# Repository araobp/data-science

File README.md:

# Edge AI and Digital Signal Processing

Hand gesture "Paper" captured with [AMG8833 infrared array sensor (8x8 resolution)](https://industrial.panasonic.com/products/pt/grid-eye/models/AMG8833), and its DCT Type-II coefficients.

Paco de Lucia's Picado from ["Cepa Andaluza" (Bulerias)](https://youtu.be/NIKWBdthzg4?si=O71p1-v_ynUPurbq) captured with my "Acoustic Feature Camera" device.

In this project, I pick up some of my achievements on edge AI from my past projects, and update them with the latest IDEs such as STM32CubeIDE or Android Studio.

I will also try to create Generative Art with edge AI in this project.

My past projects on edge AI:
- [acoustic-features](https://github.com/araobp/acoustic-features)
- [android-aed](https://github.com/araobp/android-aed)
- [stm32-mcu](https://github.com/araobp/stm32-mcu)

## Project 1: Rock Paper Scissors Machine

- "Rock Paper Scissors" game machine with NUCLEO-L476RG board.
- Digital Twin of the machine made with Blender.

=> **[Rock Paper Scissors](./RockPaperScissors)**

## Project 2: Acoustic Scene Classification (Work in progress)

Note: I have stopped developing this on STM32L4, because X-CUBE-AI has some problems. I will start developing Acoustic Scene Classification on Android instead.

=> **[Acoustic Scene Classification with Android (work in progress)](./AcousticSceneClassification)**

=> [Audio Signal Processing with STM32L4 (terminated)](./AudioSignalProcessingWithSTM32L4.md)

---
## Misc

### [Arduino-version of the thermography](misc/Arduino)

Make Jupyter Notebook collect data from this Arduino version of the thermograpy device with Panasonic AMG8833.

This is me.

### Learning by Doing

### DSP-related

- [Digital Audio Processing](misc/DigitalAudioProcessing)
- [Speech Processing for AI](misc/SpeechProcessing)

### Others

- [CIFAR 10](misc/CIFAR10): The best accuracy I have ever achieved is 75%...
- [MINIST](misc/MNIST)
- [IMDb](misc/IMDb)
- [Titanic](misc/Titanic)
- [Audio](misc/Audio)

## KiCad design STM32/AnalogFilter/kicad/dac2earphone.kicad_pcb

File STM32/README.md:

# Rock Paper Scissors with CubeIDE and STM32Cube.AI

Board: NUCLEO-L476RG board (STM32L476RGT6 Microcontroller)

### Arudino shield for Panasonic AMG8833

I designed my original Arduino shield for AMG8833 in 2019. Refer to [this page](https://github.com/araobp/stm32-mcu/tree/master/NUCLEO-F401RE/Thermography). I use this board with Nucleo L476RG.

=> [Schematic](https://github.com/araobp/stm32-mcu/blob/master/NUCLEO-F401RE/Thermography/kicad/arduino_board.pdf)

### Thermography (without AI)

This project is just a thermography app with Panasonic AMG8833 (no AI):
- [Thermography](Thermography)

Its GUI is in this folder: [GUI(Python3)](Thermography/GUI)

```
[NUCLEO L476RG] --- UART (VCP via ST-Link) --- COM port [Thermography GUI]
```

### Rock Paper Scissors (with AI)

This project is AI Rock Paper Scissors with Panasonic AMG8333:
- [RockPaperScissors](RockPaperScissors)

Its recognition performance is good.

This experiment proves that twenty of DCT Type-II coefficients with a small DNN is sufficient for recognizing rock/paper/scissors. 

### CubeMX-related problems I faced in this development

***printf issues***

I faced malloc-related build errors after I added "printf" (_write() function) to "main.c". The following setting solved the problem.

The marked part must be elased.

***Build errors***

Building with source code generated by X-Cube-AI results in a lot of errors. Building twice resolves this problem. Why?

***Lack of documentation***

I need example source codes of STM32Cube.AI. This page might help:
https://wiki.stmicroelectronics.cn/stm32mcu/wiki/AI:How_to_perform_motion_sensing_on_STM32L4_IoTnode#Add_AI_bootstrapping_functions

## Other Basic apps (not relevant to Rock Paper Scissors)

- [HelloWorld](HelloWorld)
- [Clock](Clock)

### I2C pin assignment for Arduino shield

Arduino shield uses PB8 and PB9 for I2C SCL and SDA.

## References

### CMSIS-DSP library

Refer to the following site: Google search "Configuring DSP libraries on STM32CubeIDE"

[API reference](https://arm-software.github.io/CMSIS_5/General/html/index.html)

## References

- https://stackoverflow.com/questions/59395181/cmsis-dsp-in-stm32cubeide

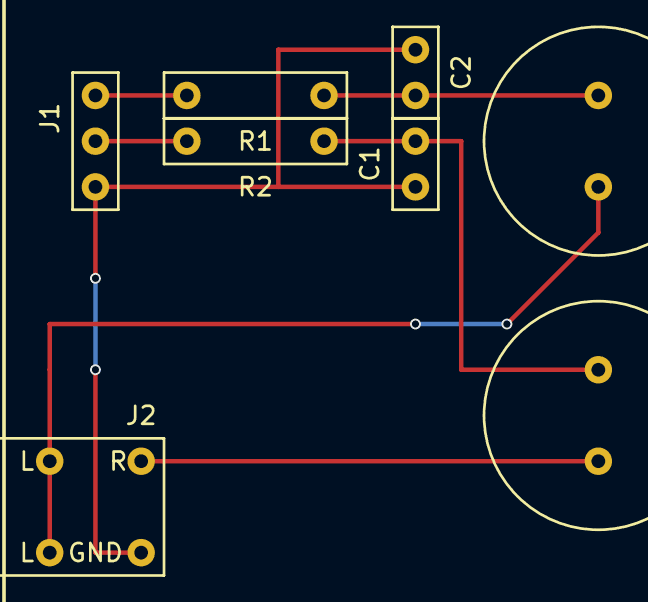
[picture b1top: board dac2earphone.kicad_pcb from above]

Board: 2 copper layers, 8 parts (0 on the bottom side), 7 nets.

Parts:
C1, C2: 0.1u; Capacitor
C3, C4: 220u; audio_capacitor
J1: Conn_01x03_Male; Pin_Header_3P
J2: Conn_01x03_Male; audio_jack_3.5mm
R1, R2: 120; Register

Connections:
GND: C1.2, C2.2, J1.3, J2.1
unnamed: C1.1, C4.2, R2.1
unnamed: C2.1, C3.2, R1.1
unnamed: C3.1, J2.3
unnamed: C4.1, J2.2
unnamed: J1.1, R1.2
unnamed: J1.2, R2.2

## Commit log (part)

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2023-09-21 Rename DigitalAudioProcessing1 -- Audio Waveform.ipynb to DigitalAudioProcessing1_AudioWaveform.ipynb
2023-09-21 Rename DigitalAudioProcessing2 -- Descrete Fourier Transform.ipynb to DigitalAudioProcessing2_DescreteFourierTransform.ipynb
2023-09-21 Rename DigitalAudioProcessing3 -- RFFT and Windowing.ipynb to DigitalAudioProcessing3_RFFTandWindowing.ipynb
2023-10-31 directory structure change
2023-10-31 Rename RockPaperScissors.md to README.md
2023-10-31 Rename AcousticSceneClassification.md to README.md
2023-10-31 Rename RockPaperScissorsMachine.md to RockPaperScissors.md
2023-10-31 Rename RockPaperScissors.md to RockPaperScissorsMachine.md
